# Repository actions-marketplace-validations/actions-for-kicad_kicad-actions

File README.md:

# KiCad actions

This GitHub Action provides a way to run [KiCad](https://www.kicad.org/) in your CI pipelines.

# 🧾 Versioning

Every release of this action is tagged with two version numbers:

- 📦 **Action version** — Version of this GitHub Action
- ⚙️ **KiCad version** — Version of KiCad used inside the action

The releases are formatted as follows:

```
v{action-version}-k{KiCad-version}
```

For example `v1-k9.0`. This houses version one of this action and version `9.0` from KiCad.

The KiCad version can be set to the `minor` or `patch` version. For example:

- Use `v{action-version}-k9.0` to to get the latest version of KiCad `v9.0` (for example `v9.0.2`).
- Use `v{action-version}-k9.0.1` to to get the specific requested version of KiCad.

Check the [releases](https://github.com/actions-for-kicad/kicad-actions/releases) to see all available versions.

# 🚀 Usage

See [action.yml](action.yml)

```yaml
steps:
  - name: Checkout Repository
    uses: actions/checkout@v4

  - name: Run KiCad actions
    uses: actions-for-kicad/kicad-actions@v1-k9.0
    with:
      schematic_file_name: ./file.kicad_sch
      symbol_libraries: "symbol-library=./symbol-library.kicad_sym"
      run_erc: true
      schematic_output_pdf: true

      pcb_file_name: ./file.kicad_pcb
      footprint_libraries: "footprint-library=./footprint-library.pretty"
      run_drc: true
      pcb_output_gerbers_and_drill: true

  - name: Upload schematic
    uses: actions/upload-artifact@v4
    with:
      name: Schematic
      path: ./schematic.pdf

  - name: Upload gerbers and drill file
    uses: actions/upload-artifact@v4
    with:
      name: Gerbers
      path: ./gerbers
```

# 📥 Inputs

## `schematic_file_name`

Required: `false`\
\
Description: Location of the `.kicad_sch` file.

## `symbol_libraries`

Required: `false`\
\
Description: Comma-separated list of symbol libraries in the format name=path. The path should be relative to the `.kicad_pro` file.

## `run_erc`

Required: `false`\
Default: `false`\
\
Description: Run the ERC (Electrical Rules Check) on the schematic.

## `erc_output_file_name`

Required: `false`\
Default: `erc.rpt`\
\
Description: Output file name of ERC report.

## `schematic_output_pdf`

Required: `false`\
Default: `false`\
\
Description: Run the PDF export of the schematic.

## `schematic_output_pdf_file_name`

Required: `false`\
Default: `schematic.pdf`\
\
Description: Output file name of PDF schematic.

## `schematic_output_black_white`

Required: `false`\
Default: `false`\
\
Description: Run the PDF, SVG, DXF, and PS schematic export in black and white.

## `schematic_output_svg`

Required: `false`\
Default: `false`\
\
Description: Run the SVG export of the schematic.

## `schematic_output_svg_folder_name`

Required: `false`\
Default: `schematics`\
\
Description: Output folder name of SVG schematic.

## `schematic_output_dxf`

Required: `false`\
Default: `false`\
\
Description: Run the DXF export of the schematic.

## `schematic_output_dxf_folder_name`

Required: `false`\
Default: `schematics`\
\
Description: Output folder name of DXF schematic.

## `schematic_output_hpgl`

Required: `false`\
Default: `false`\
\
Description: Run the HPGL export of the schematic.

## `schematic_output_hpgl_folder_name`

Required: `false`\
Default: `schematics`\
\
Description: Output folder name of HPGL schematic.

## `schematic_output_ps`

Required: `false`\
Default: `false`\
\
Description: Run the PS export of the schematic.

## `schematic_output_ps_folder_name`

Required: `false`\
Default: `schematics`\
\
Description: Output folder name of PS schematic.

## `schematic_output_bom`

Required: `false`\
Default: `false`\
\
Description: Run the BOM (Bill of Materials) export of the schematic.

## `schematic_output_bom_file_name`

Required: `false`\
Default: `bom.csv`\
\
Description: Output file name of the BOM.

## `schematic_output_bom_fields`

Required: `false`\
Default: `Reference,Value,Footprint,${QUANTITY},${DNP}`\
\
Description: Output fields in the BOM file. `*` includes all fields.

## `schematic_output_bom_labels`

Required: `false`\
Default: `Refs,Value,Footprint,Qty,DNP`\
\
Description: Output labels in the BOM file.

## `schematic_output_netlist`

Required: `false`\
Default: `false`\
\
Description: Run the netlist export of the schematic.

## `schematic_output_netlist_file_name`

Required: `false`\
Default: `netlist.net`\
\
Description: Output file name of the netlist.

## `pcb_file_name`

Required: `false`\
\
Description: Location of the `.kicad_pcb` file.

## `footprint_libraries`

Required: `false`\
\
Description: Comma-separated list of footprint libraries in the format name=path. The path should be relative to the `.kicad_pro` file.

## `run_drc`

Required: `false`\
Default: `false`\
\
Description: Run the DRC (Design Rules Check) on the PCB.

## `drc_output_file_name`

Required: `false`\
Default: `drc.rpt`\
\
Description: Output file name of DRC report.

## `pcb_output_drill`

Required: `false`\
Default: `false`\
\
Description: Run the drill export of the PCB.

## `pcb_output_drill_folder_name`

Required: `false`\
Default: `drill`\
\
Description: Output folder name of drill file.

## `pcb_output_drill_format`

Required: `false`\
Default: `excellon`\
\
Description: Format of the drill file. Options:

- `excellon`
- `gerber`

## `pcb_output_gerbers`

Required: `false`\
Default: `false`\
\
Description: Run the gerber export of the PCB.

## `pcb_output_gerbers_folder_name`

Required: `false`\
Default: `gerbers`\
\
Description: Output folder name of gerber files.

## `pcb_output_layers`

Required: `false`\
\
Description: Output layers of the PCB.

## `pcb_output_gerbers_and_drill`

Required: `false`\
Default: `false`\
\
Description: Run the gerber and drill export of the PCB.

## `pcb_output_gerbers_and_drill_folder_name`

Required: `false`\
Default: `gerbers`\
\
Description: Output folder name of gerber and drill files.

## `pcb_output_dxf`

Required: `false`\
Default: `false`\
\
Description: Run the DXF export of the PCB.

## `pcb_output_dxf_folder_name`

Required: `false`\
Default: `dxf`\
\
Description: Output folder name of DXF PCB.

## `pcb_output_pdf`

Required: `false`\
Default: `false`\
\
Description: Run the PDF export of the PCB.

## `pcb_output_pdf_file_name`

Required: `false`\
Default: `pcb.pdf`\
\
Description: Output file name of PDF PCB.

## `pcb_output_black_white`

Required: `false`\
Default: `false`\
\
Description: Run the PDF and SVG PCB export in black and white.

## `pcb_output_svg`

Required: `false`\
Default: `false`\
\
Description: Run the SVG export of the PCB.

## `pcb_output_svg_file_name`

Required: `false`\
Default: `pcb.svg`\
\
Description: Output file name of SVG PCB.

## `pcb_output_pos`

Required: `false`\
Default: `false`\
\
Description: Run the POS export of the PCB.

## `pcb_output_pos_file_name`

Required: `false`\
Default: `pcb.pos`\
\
Description: Output file name of POS PCB.

## `pcb_output_pos_format`

Required: `false`\
Default: `ascii`\
\
Description: Format of the POS file. Options:

- `ascii`
- `csv`
- `gerber`

## `pcb_output_pos_side`

Required: `false`\
Default: `both`\
\
Description: Side of the POS file. Options:

- `front`
- `back`
- `both`

> **Note:** both is not supported by gerber.

## `pcb_output_ipc2581`

Required: `false`\
Default: `false`\
\
Description: Run the IPC-2581 export of the PCB.

## `pcb_output_ipc2581_file_name`

Required: `false`\
Default: `pcb.xml`\
\
Description: Output file name of IPC-2581 PCB.

## `pcb_output_step`

Required: `false`\
Default: `false`\
\
Description: Run the STEP export of the PCB.

## `pcb_output_step_file_name`

Required: `false`\
Default: `pcb.step`\
\
Description: Output file name of STEP PCB.

## `pcb_output_image`

Required: `false`\
Default: `false`\
\
Description: Run the image export of the PCB.

## `pcb_output_image_file_name`

Required: `false`\
Default: `pcb.png`\
\
Description: Output file name of image PCB. Must end in '.png', '.jpg', '.jpeg'.

## `pcb_output_image_side`

Required: `false`\
Default: `top`\
\
Description: Side of the image PCB. Options:

- `top`
- `bottom`
- `left`
- `right`
- `front`
- `back`

## `pcb_output_image_background`

Required: `false`\
Default: `default`\
\
Description: Background of the image PCB. Options:

- `default`
- `transparent`
- `opaque`

For PNG files, default is transparent. For JPG files, default is opaque.

## `pcb_output_image_width`

Required: `false`\
Default: `1600`\
\
Description: Width of the image PCB in pixels.

## `pcb_output_image_height`

Required: `false`\
Default: `900`\
\
Description: Height of the image PCB in pixels.

## `pcb_output_image_floor`

Required: `false`\
Default: `false`\
\
Description: Enables floor, shadows and post-processing.

# 📤 Outputs

This action exports multiple files based on the inputs that are given.

# 📄 License

The scripts and documentation in this project are released under the [MIT license](LICENSE).

# 🧑‍💻 Contributions

Contributions are welcome! Please help me expand and maintain this repository.

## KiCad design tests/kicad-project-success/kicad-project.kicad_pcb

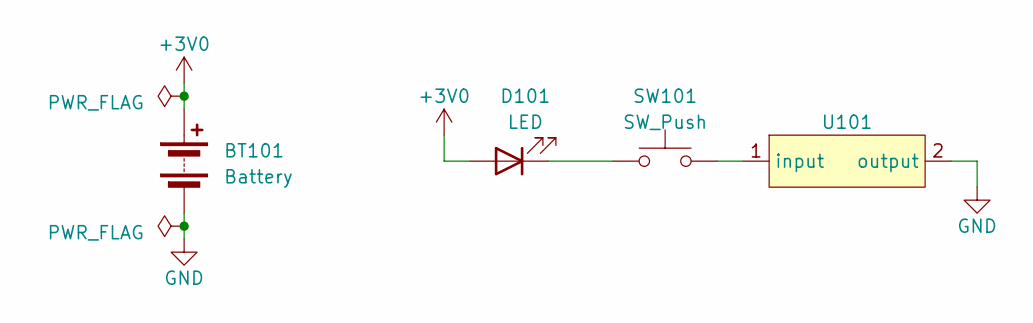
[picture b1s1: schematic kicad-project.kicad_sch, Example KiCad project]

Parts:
BT101: Battery; BatteryHolder_Bulgin_BX0036_1xC
D101: LED; LED_D3.0mm_Horizontal_O1.27mm_Z2.0mm
SW101: SW_Push; SW_PUSH_6mm
U101: Line

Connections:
+3V0: BT101.1 (+), D101.2 (A)
GND: BT101.2 (-), U101.2 (output)
unnamed: D101.1 (K), SW101.1
unnamed: SW101.2, U101.1 (input)

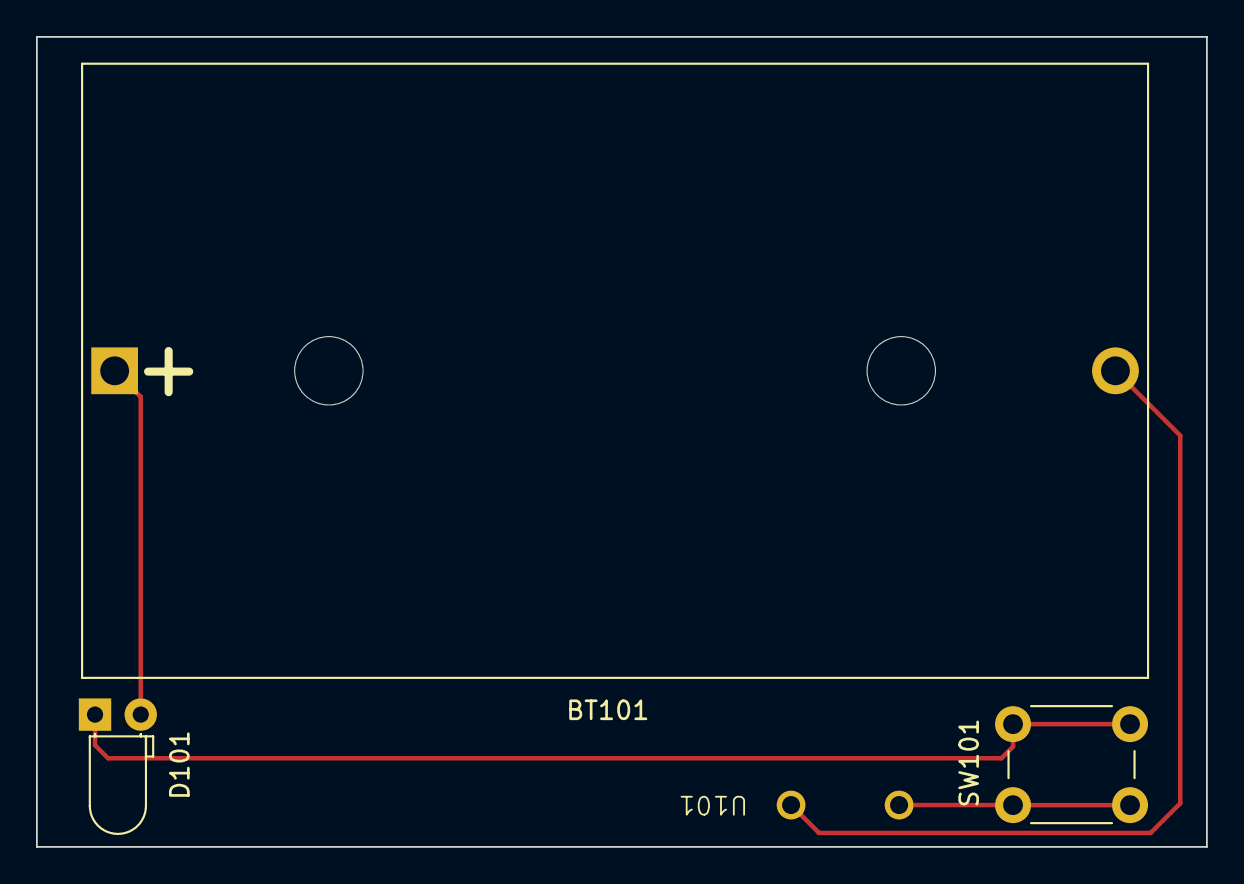
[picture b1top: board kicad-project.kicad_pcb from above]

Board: 2 copper layers, 65.0 x 45.0 mm, 4 parts (0 on the bottom side), 4 nets.

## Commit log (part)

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2025-04-01 Added readme
2025-04-01 Create LICENSE
2025-04-01 Updated file permissions
2025-04-01 Now building based on a new tag
2025-04-01 Updated build script
2025-04-01 Fixed build pipeline
2025-04-01 Fixed build pipeline new try
2025-04-01 Updated kicad versions
2025-04-01 Added more permissions
2025-04-01 Added erc check
2025-04-01 Fixed file input
2025-04-01 Combined ERC and DRC tests in one single job
2025-04-01 Added check for file check
2025-04-02 Fixed kicad commands
2025-04-02 Made the code more readable and robust
2025-04-02 Added first PCB outputs and tests
2025-04-02 Added dxf export
2025-04-02 Fixed minor export issues
2025-04-02 Fixed check loop
2025-04-03 Added gerber drill output and fixed test
2025-04-03 Added different pick and place outputs and tests
2025-04-03 Finalized tests and error checking
2025-04-03 Fixed full test
2025-04-03 Added manual run on the main version tag
2025-04-05 Fixed main version tag
2025-04-19 Added bom export options
2025-05-02 Added debug
2025-05-02 Added debug code
2025-05-03 Added footprint library support
2025-05-03 Updated documentation
2025-05-07 Fix the zip bug
2025-05-07 Fix bug in the tests and make no files fail the tets
2025-05-09 Added auto update kicad build versions workflow
2025-05-09 Added github app to fix permission issue
2025-05-09 Fixed more tag versions
2025-05-09 Fixed permission issue again
2025-05-09 Tried to fix permission issue
2025-05-10 Updated test
2025-05-10 Renamed file
2025-05-10 Fixed empty file when no new versions
2025-05-10 Put version back
2025-05-14 Added image export to render
2025-05-24 Update issue templates
2025-06-29 Inject CodeQL file
2025-06-29 Bump github/codeql-action from 2.1.36 to 3.29.1
    Bumps [github/codeql-action](https://github.com/github/codeql-action) from 2.1.36 to 3.29.1.
    - [Release notes](https://github.com/github/codeql-action/releases)
    - [Changelog](https://github.com/github/codeql-action/blob/main/CHANGELOG.md)
    - [Commits](https://github.com/github/codeql-action/compare/a669cc5936cc5e1b6a362ec1ff9e410dc570d190...39edc492dbe16b1465b0cafca41432d857bdb31a)
    ---
    updated-dependencies:
2025-08-11 Bump github/codeql-action from 2.1.36 to 3.29.8
    Bumps [github/codeql-action](https://github.com/github/codeql-action) from 2.1.36 to 3.29.8.
    - [Release notes](https://github.com/github/codeql-action/releases)
    - [Changelog](https://github.com/github/codeql-action/blob/main/CHANGELOG.md)
    - [Commits](https://github.com/github/codeql-action/compare/a669cc5936cc5e1b6a362ec1ff9e410dc570d190...76621b61decf072c1cee8dd1ce2d2a82d33c17ed)
    ---
    updated-dependencies:
2025-08-25 Bump actions/checkout from 3.1.0 to 5.0.0
    Bumps [actions/checkout](https://github.com/actions/checkout) from 3.1.0 to 5.0.0.
    - [Release notes](https://github.com/actions/checkout/releases)
    - [Commits](https://github.com/actions/checkout/compare/v3.1.0...v5)
    ---
    updated-dependencies:
    - dependency-name: actions/checkout
2025-09-01 Bump github/codeql-action from 2.1.36 to 3.30.0
    Bumps [github/codeql-action](https://github.com/github/codeql-action) from 2.1.36 to 3.30.0.
    - [Release notes](https://github.com/github/codeql-action/releases)
    - [Changelog](https://github.com/github/codeql-action/blob/main/CHANGELOG.md)
    - [Commits](https://github.com/github/codeql-action/compare/a669cc5936cc5e1b6a362ec1ff9e410dc570d190...2d92b76c45b91eb80fc44c74ce3fce0ee94e8f9d)
    ---
    updated-dependencies:
2025-09-08 Bump github/codeql-action from 2.1.36 to 3.30.1
    Bumps [github/codeql-action](https://github.com/github/codeql-action) from 2.1.36 to 3.30.1.
    - [Release notes](https://github.com/github/codeql-action/releases)
    - [Changelog](https://github.com/github/codeql-action/blob/main/CHANGELOG.md)
    - [Commits](https://github.com/github/codeql-action/compare/a669cc5936cc5e1b6a362ec1ff9e410dc570d190...f1f6e5f6af878fb37288ce1c627459e94dbf7d01)
    ---
    updated-dependencies:
2025-09-29 Bump github/codeql-action from 2.1.36 to 3.30.5
    Bumps [github/codeql-action](https://github.com/github/codeql-action) from 2.1.36 to 3.30.5.
    - [Release notes](https://github.com/github/codeql-action/releases)
    - [Changelog](https://github.com/github/codeql-action/blob/main/CHANGELOG.md)
    - [Commits](https://github.com/github/codeql-action/compare/a669cc5936cc5e1b6a362ec1ff9e410dc570d190...3599b3baa15b485a2e49ef411a7a4bb2452e7f93)
    ---
    updated-dependencies:
2025-10-13 Bump github/codeql-action from 2.1.36 to 4.30.8
    Bumps [github/codeql-action](https://github.com/github/codeql-action) from 2.1.36 to 4.30.8.
    - [Release notes](https://github.com/github/codeql-action/releases)
    - [Changelog](https://github.com/github/codeql-action/blob/main/CHANGELOG.md)
    - [Commits](https://github.com/github/codeql-action/compare/a669cc5936cc5e1b6a362ec1ff9e410dc570d190...f443b600d91635bebf5b0d9ebc620189c0d6fba5)
    ---
    updated-dependencies:
2025-10-27 Bump actions/upload-artifact from 4 to 5
    Bumps [actions/upload-artifact](https://github.com/actions/upload-artifact) from 4 to 5.
    - [Release notes](https://github.com/actions/upload-artifact/releases)
    - [Commits](https://github.com/actions/upload-artifact/compare/v4...v5)
    ---
    updated-dependencies:
    - dependency-name: actions/upload-artifact
2025-11-03 Bump github/codeql-action from 2.1.36 to 4.31.2
    Bumps [github/codeql-action](https://github.com/github/codeql-action) from 2.1.36 to 4.31.2.
    - [Release notes](https://github.com/github/codeql-action/releases)
    - [Changelog](https://github.com/github/codeql-action/blob/main/CHANGELOG.md)
    - [Commits](https://github.com/github/codeql-action/compare/a669cc5936cc5e1b6a362ec1ff9e410dc570d190...0499de31b99561a6d14a36a5f662c2a54f91beee)
    ---
    updated-dependencies:
2025-12-01 Bump github/codeql-action from 2.1.36 to 4.31.6
    Bumps [github/codeql-action](https://github.com/github/codeql-action) from 2.1.36 to 4.31.6.
    - [Release notes](https://github.com/github/codeql-action/releases)
    - [Changelog](https://github.com/github/codeql-action/blob/main/CHANGELOG.md)
    - [Commits](https://github.com/github/codeql-action/compare/a669cc5936cc5e1b6a362ec1ff9e410dc570d190...fe4161a26a8629af62121b670040955b330f9af2)
    ---
    updated-dependencies:
2025-12-05 Bump actions/checkout from 3.1.0 to 6.0.0
    Bumps [actions/checkout](https://github.com/actions/checkout) from 3.1.0 to 6.0.0.
    - [Release notes](https://github.com/actions/checkout/releases)
    - [Commits](https://github.com/actions/checkout/compare/v3.1.0...v6)
    ---
    updated-dependencies:
    - dependency-name: actions/checkout
2025-12-08 Bump github/codeql-action from 2.1.36 to 4.31.7
    Bumps [github/codeql-action](https://github.com/github/codeql-action) from 2.1.36 to 4.31.7.
    - [Release notes](https://github.com/github/codeql-action/releases)
    - [Changelog](https://github.com/github/codeql-action/blob/main/CHANGELOG.md)
    - [Commits](https://github.com/github/codeql-action/compare/a669cc5936cc5e1b6a362ec1ff9e410dc570d190...cf1bb45a277cb3c205638b2cd5c984db1c46a412)
    ---
    updated-dependencies:
2025-12-15 Bump github/codeql-action from 2.1.36 to 4.31.8
    Bumps [github/codeql-action](https://github.com/github/codeql-action) from 2.1.36 to 4.31.8.
    - [Release notes](https://github.com/github/codeql-action/releases)
    - [Changelog](https://github.com/github/codeql-action/blob/main/CHANGELOG.md)
    - [Commits](https://github.com/github/codeql-action/compare/a669cc5936cc5e1b6a362ec1ff9e410dc570d190...1b168cd39490f61582a9beae412bb7057a6b2c4e)
    ---
    updated-dependencies:
2026-01-19 Bump github/codeql-action from 2.1.36 to 4.31.10
    Bumps [github/codeql-action](https://github.com/github/codeql-action) from 2.1.36 to 4.31.10.
    - [Release notes](https://github.com/github/codeql-action/releases)
    - [Changelog](https://github.com/github/codeql-action/blob/main/CHANGELOG.md)
    - [Commits](https://github.com/github/codeql-action/compare/a669cc5936cc5e1b6a362ec1ff9e410dc570d190...cdefb33c0f6224e58673d9004f47f7cb3e328b89)
    ---
    updated-dependencies:
2026-01-26 Bump actions/checkout from 3.1.0 to 6.0.2
    Bumps [actions/checkout](https://github.com/actions/checkout) from 3.1.0 to 6.0.2.
    - [Release notes](https://github.com/actions/checkout/releases)
    - [Commits](https://github.com/actions/checkout/compare/v3.1.0...v6.0.2)
    ---
    updated-dependencies:
    - dependency-name: actions/checkout
2026-02-09 Bump github/codeql-action from 2.1.36 to 4.32.2
    Bumps [github/codeql-action](https://github.com/github/codeql-action) from 2.1.36 to 4.32.2.
    - [Release notes](https://github.com/github/codeql-action/releases)
    - [Changelog](https://github.com/github/codeql-action/blob/main/CHANGELOG.md)
    - [Commits](https://github.com/github/codeql-action/compare/a669cc5936cc5e1b6a362ec1ff9e410dc570d190...45cbd0c69e560cd9e7cd7f8c32362050c9b7ded2)
    ---
    updated-dependencies:
2026-02-16 Bump github/codeql-action from 2.1.36 to 4.32.3
    Bumps [github/codeql-action](https://github.com/github/codeql-action) from 2.1.36 to 4.32.3.
    - [Release notes](https://github.com/github/codeql-action/releases)
    - [Changelog](https://github.com/github/codeql-action/blob/main/CHANGELOG.md)
    - [Commits](https://github.com/github/codeql-action/compare/a669cc5936cc5e1b6a362ec1ff9e410dc570d190...9e907b5e64f6b83e7804b09294d44122997950d6)
    ---
    updated-dependencies:
2026-03-22 Bump github/codeql-action from 2.1.36 to 4.34.1
    Bumps [github/codeql-action](https://github.com/github/codeql-action) from 2.1.36 to 4.34.1.
    - [Release notes](https://github.com/github/codeql-action/releases)
    - [Changelog](https://github.com/github/codeql-action/blob/main/CHANGELOG.md)
    - [Commits](https://github.com/github/codeql-action/compare/a669cc5936cc5e1b6a362ec1ff9e410dc570d190...38697555549f1db7851b81482ff19f1fa5c4fedc)
    ---
    updated-dependencies:
2026-04-19 Bump github/codeql-action from 2.1.36 to 4.35.2
    Bumps [github/codeql-action](https://github.com/github/codeql-action) from 2.1.36 to 4.35.2.
    - [Release notes](https://github.com/github/codeql-action/releases)
    - [Changelog](https://github.com/github/codeql-action/blob/main/CHANGELOG.md)
    - [Commits](https://github.com/github/codeql-action/compare/a669cc5936cc5e1b6a362ec1ff9e410dc570d190...95e58e9a2cdfd71adc6e0353d5c52f41a045d225)
    ---
    updated-dependencies:
2026-05-10 Bump github/codeql-action from 2.1.36 to 4.35.4
    Bumps [github/codeql-action](https://github.com/github/codeql-action) from 2.1.36 to 4.35.4.
    - [Release notes](https://github.com/github/codeql-action/releases)
    - [Changelog](https://github.com/github/codeql-action/blob/main/CHANGELOG.md)
    - [Commits](https://github.com/github/codeql-action/compare/a669cc5936cc5e1b6a362ec1ff9e410dc570d190...68bde559dea0fdcac2102bfdf6230c5f70eb485e)
    ---
    updated-dependencies:
2026-05-24 Bump github/codeql-action from 2.1.36 to 4.36.0
    Bumps [github/codeql-action](https://github.com/github/codeql-action) from 2.1.36 to 4.36.0.
    - [Release notes](https://github.com/github/codeql-action/releases)
    - [Changelog](https://github.com/github/codeql-action/blob/main/CHANGELOG.md)
    - [Commits](https://github.com/github/codeql-action/compare/a669cc5936cc5e1b6a362ec1ff9e410dc570d190...7211b7c8077ea37d8641b6271f6a365a22a5fbfa)
    ---
    updated-dependencies:
